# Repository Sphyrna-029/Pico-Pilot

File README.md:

# Pico-Pilot WIP
A auto pilot for land/air/sea based robots built on the RP2350B/RP2354B. Supports 2D waypoint missions, telemetry, and custom vehicle configuration. 
Requires simple_pid and warnings packages.

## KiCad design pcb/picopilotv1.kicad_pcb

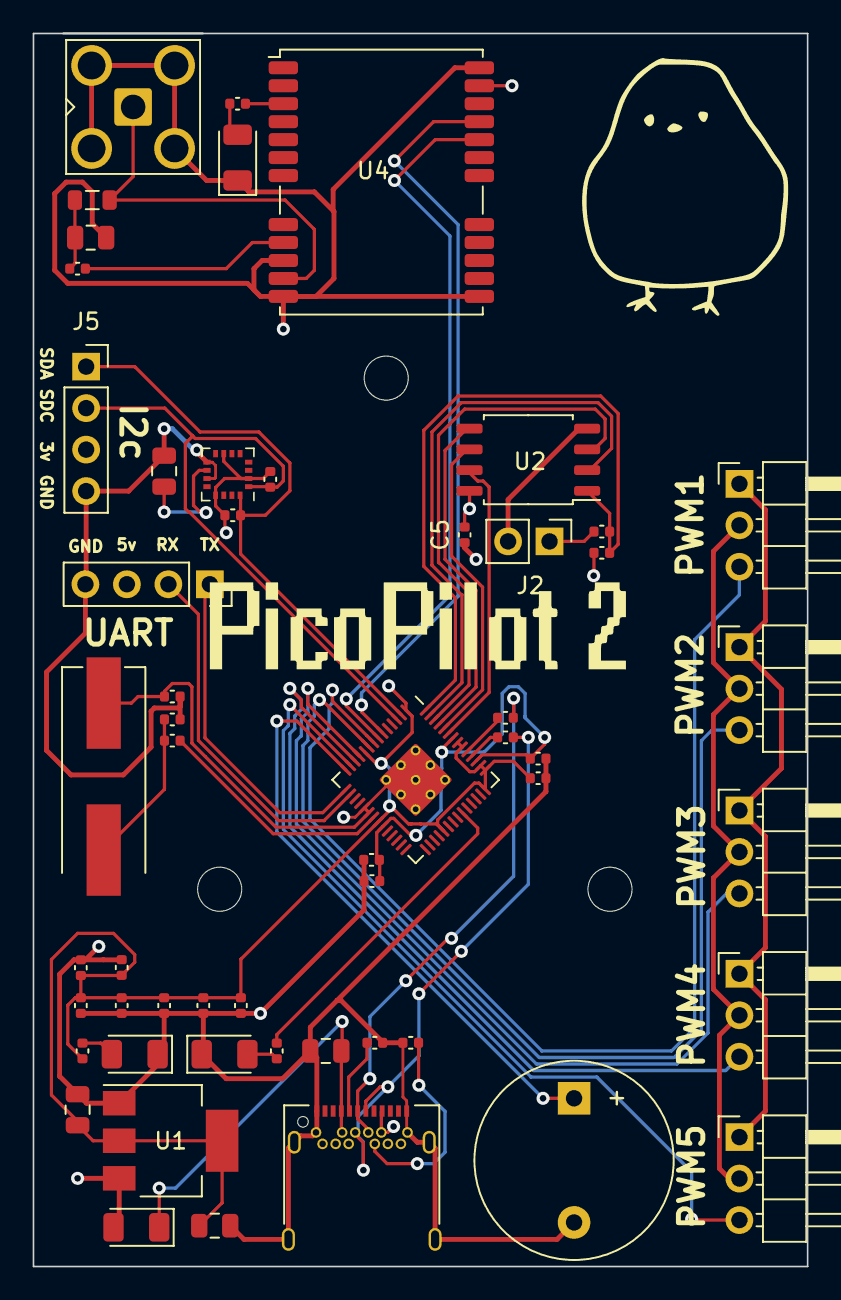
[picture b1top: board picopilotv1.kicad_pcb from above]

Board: 4 copper layers, 47.4 x 75.5 mm, 58 parts (0 on the bottom side), 41 nets.

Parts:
BZ1: Buzzer; Buzzer_12x9.5RM7.6
C1, C4, C17: 10u; C_0805_2012Metric
C2, C3: 27p; C_0402_1005Metric
C5, C6, C7, C9, C11, C12, C13, C14, C15, C16: 100n; C_0402_1005Metric
C8, C10: 1u; C_0402_1005Metric
C18: 10n; C_0805_2012Metric
C19: 4.7uf; C_0805_2012Metric
D1: DIODE; D_1206_3216Metric
D2, D3, D4: LED; LED_1206_3216Metric
H1, H2, H3, H4: MountingHole; MountingHole_2.7mm_M2.5
J1, J5: Telemetry; PinSocket_1x04_P2.54mm_Vertical
J2: Conn_01x02; PinHeader_1x02_P2.54mm_Vertical
J3: USB_C_Receptacle_USB2.0; USB_C_Receptacle_Amphenol_12401548E4-2A
J4: Conn_Coaxial; SMA_Amphenol_901-143_Horizontal
L1: 27nh; L_0805_2012Metric
P1: PWM1; PinHeader_1x03_P2.54mm_Horizontal
P2: PWM2; PinHeader_1x03_P2.54mm_Horizontal
P3: PWM3; PinHeader_1x03_P2.54mm_Horizontal
P4: PWM4; PinHeader_1x03_P2.54mm_Horizontal
P5: PWM5; PinHeader_1x03_P2.54mm_Horizontal
R1, R5, R6, R7, R9: 1k; C_0402_1005Metric
R2: DNF; C_0402_1005Metric
R3, R4: 27; C_0402_1005Metric
R8: 10; C_0402_1005Metric
R10, R11: 4.7k; C_0402_1005Metric
R13, R14: 5.11k; C_0402_1005Metric
U1: NCP1117-3.3_SOT223; SOT-223-3_TabPin2
U2: W25Q128JVS; SOIC-8_5.23x5.23mm_P1.27mm
U3: RP2040; RP2040-QFN-56
U4: NEO-M8M; ublox_NEO
U5: IST8308; LGA-16_3x3mm_P0.5mm
Y1: ABLS-12.000MHZ-B4-T; Crystal_SMD_HC49-US

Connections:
+1V1: C6.1, C7.1, C8.1, U3.23 (DVDD), U3.45 (VREG_VOUT), U3.50 (DVDD)
+3V3: C4.1, C5.1, C9.1, C10.1, C11.1, C12.1, C13.1, C14.1, C15.1, C16.1, C17.1, J5.3, R2.1, R6.1, R10.1, R11.1, U1.2 (VO), U2.8 (VCC), U3.1 (IOVDD), U3.10 (IOVDD), U3.22 (IOVDD), U3.33 (IOVDD), U3.42 (IOVDD), U3.43 (ADC_AVDD), U3.44 (VREG_IN), U3.48 (USB_VDD), U3.49 (IOVDD), U4.23 (VCC), U5.2 (AVDD), U5.7 (VPP), U5.13 (DVDD)
+5V: D1.2 (A), J1.3, P1.2, P2.2, P3.2, P4.2, P5.2, U1.3 (VI)
/GPIO0: J5.1, R11.2, U3.2 (GPIO0), U5.16 (SDA)
/GPIO1: J5.2, R10.2, U3.3 (GPIO1), U5.1 (SCL)
/GPIO4: U3.6 (GPIO4), U4.21 (RXD/SPI_MOSI)
/GPIO5: U3.7 (GPIO5), U4.20 (TXD/SPI_MISO)
/GPIO6: P1.3, U3.8 (GPIO6)
/GPIO7: P2.3, U3.9 (GPIO7)
/GPIO8: P3.3, U3.11 (GPIO8)
/GPIO9: P4.3, U3.12 (GPIO9)
/GPIO10: P5.3, U3.13 (GPIO10)
/GPIO11: BZ1.1 (-), U3.14 (GPIO11)
/GPIO12: J1.1, U3.15 (GPIO12)
/GPIO13: J1.2, U3.16 (GPIO13)
/GPIO25: R7.1, U3.37 (GPIO25)
/QSPI_SCLK: U2.6 (CLK), U3.52 (QSPI_SCLK)
/QSPI_SD0: U2.5 (DI(IO0)), U3.53 (QSPI_SD0)
/QSPI_SD1: U2.2 (DO(IO1)), U3.55 (QSPI_SD1)
/QSPI_SD2: U2.3 (IO2), U3.54 (QSPI_SD2)
/QSPI_SD3: U2.7 (IO3), U3.51 (QSPI_SD3)
/QSPI_SS: R1.1, R2.2, U2.1 (~CS), U3.56 (QSPI_SS)
/USB_D+: J3.A6 (D+), J3.B6 (D+), R3.1
/USB_D-: J3.A7 (D-), J3.B7 (D-), R4.1
/XOUT: R5.1, U3.21 (XOUT)
/~USB_BOOT: J2.1, R1.2
GND: BZ1.2 (+), C1.2, C2.1, C2.2, C3.2, C4.2, C5.2, C6.2, C7.2, C8.2, C9.2, C10.2, C11.2, C12.2, C13.2, C14.2, C15.2, C16.2, C17.2, C18.1, C19.2, D2.1 (K), D3.1 (K), D4.1 (K), J1.4, J2.2, J3.A1 (GND), J3.A12 (GND), J3.B1 (GND), J3.B12 (GND), J3.S1 (SHIELD), J4.2 (Ext), J5.4, P1.1, P2.1, P3.1, P4.1, P5.1, R13.2, R14.2, U1.1 (GND), U2.4 (GND), U3.19 (TESTEN), U3.20 (XIN), U3.57 (GND), U4.10 (GND), U4.12 (GND), U4.13 (GND), U4.24 (GND), U5.9 (VSS), U5.11 (VSS), Y1.1
unnamed: C3.1, R5.2, Y1.2
unnamed: C18.2, L1.1, R8.2
unnamed: C19.1, U5.10 (C1)
unnamed: D2.2 (A), R6.2
unnamed: D3.2 (A), R7.2
unnamed: D4.2 (A), R9.2
unnamed: J4.1 (In), L1.2, U4.11 (RF_IN)
unnamed: R3.2, U3.47 (USB_DP)
unnamed: R4.2, U3.46 (USB_DM)
unnamed: R8.1, U4.9 (VCC_RF)
unnamed: R9.1, U4.3 (TIMEPULSE)
unnamed: J3.A5 (CC1), R13.1
unnamed: J3.B5 (CC2), R14.1
VBUS: C1.1, D1.1 (K), J3.A4 (VBUS), J3.A9 (VBUS), J3.B4 (VBUS), J3.B9 (VBUS)

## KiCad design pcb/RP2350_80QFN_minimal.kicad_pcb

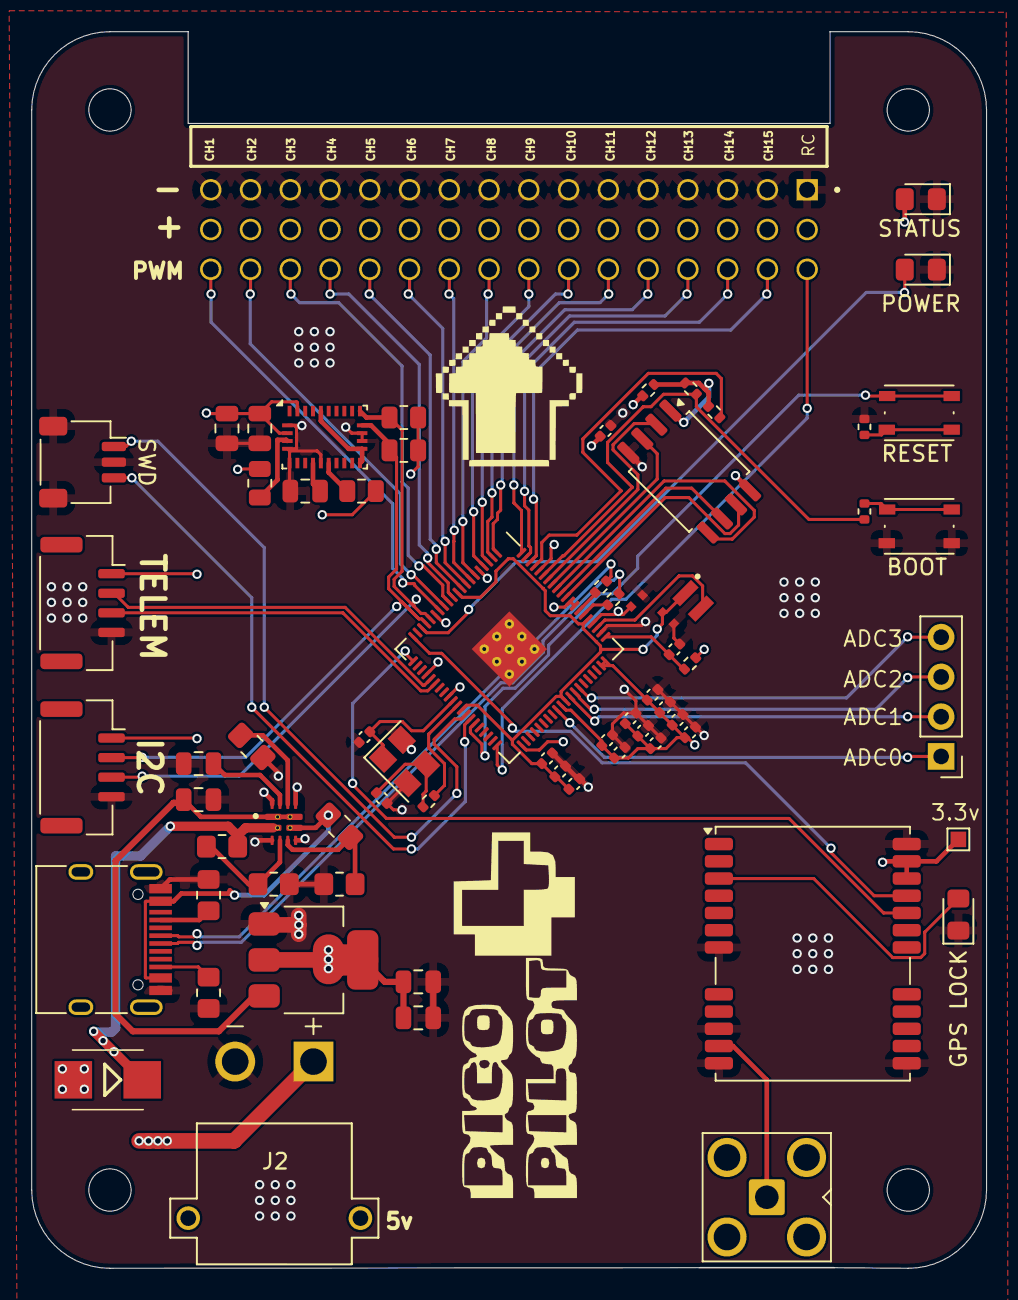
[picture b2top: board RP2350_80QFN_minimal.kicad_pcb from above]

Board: 4 copper layers, 61.0 x 79.0 mm, 72 parts (0 on the bottom side), 68 nets.

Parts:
BOOT: SW_Push; SW_Push_1P1T_NO_Vertical_Wuerth_434133025816
C1, C5, C19: 10u; C_0805_2012Metric
C2, C8, C11, C12, C13, C14, C15, C16, C17, C18, C20, C21: 100n; C_0402_1005Metric
C3, C4: 15p; C_0402_1005Metric
C6, C7: 4.7u; C_0402_1005Metric_small_pads
C9, C10: 4.7u; C_0402_1005Metric
C22: 100nF; C_0805_2012Metric
C23: 120nF; C_0805_2012Metric
C24: 6.8nF; C_0805_2012Metric
C25: 0.01u; C_0805_2012Metric
D1, D2, D3: LED; LED_0805_2012Metric_Pad1.15x1.40mm_HandSolder
D4: SS56; SMB
H1, H2, H3, H4: MountingHole; MountingHole_2.7mm_M2.5
J1: USB_C_Receptacle_USB2.0_14P; USB_C_Receptacle_HRO_TYPE-C-31-M-12
J2: XT30PW-M; AMASS_XT30PW-M
J3, J6: Conn_01x04_Pin; Molex_CLIK-Mate_502386-0470_1x04-1MP_P1.25mm_Horizontal
J4: SM03B-SRSS-TB; JST_SH_SM03B-SRSS-TB_1x03-1MP_P1.00mm_Horizontal
J5: TSW-116-08-G-T-RA; SAMTEC_TSW-116-08-G-T-RA
J7: Conn_01x04_Pin; PinHeader_1x04_P2.54mm_Vertical
J8: Conn_Coaxial_Small; SMA_Amphenol_901-143_Horizontal
L1: 3.3u; L_pol_2016
R1, R9: DNF; R_0402_1005Metric
R2, R4, R6: 1k; R_0402_1005Metric
R3: 33; R_0402_1005Metric
R5, R12: 5.1k; R_0805_2012Metric_Pad1.20x1.40mm_HandSolder
R7, R8: 27; R_0402_1005Metric
R10: 0; R_0402_1005Metric
R11, R15: 10k; R_0805_2012Metric
R13, R14: 4.7k; R_0805_2012Metric
R16: 51.1k; R_0805_2012Metric_Pad1.20x1.40mm_HandSolder
R17, R19: 23.7k; R_0805_2012Metric_Pad1.20x1.40mm_HandSolder
R18, R20: 5k; R_0805_2012Metric_Pad1.20x1.40mm_HandSolder
RESET: SW_Push; SW_Push_1P1T_NO_Vertical_Wuerth_434133025816
TP1: TestPoint; TestPoint_Pad_1.0x1.0mm
U1: RP2350_80QFN; RP2350-QFN-80-1EP_10x10_P0.4mm_EP3.4x3.4mm_ThermalVias
U2: NCP1117-3.3_SOT223; SOT-223-3_TabPin2
U3: W25Q128JVS; SOIC-8_5.23x5.23mm_P1.27mm
U4: NEO-M9N; ublox_NEO
U5: BNO055; LGA-28_5.2x3.8mm_P0.5mm
U6: TPS2121RUXR; IC_TPS2121RUXR
Y1: ABM8-272-T3; Crystal_SMD_3225-4Pin_3.2x2.5mm

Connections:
+1V1: C7.1, C8.1, C10.1, C11.1, L1.1, U1.10 (DVDD), U1.32 (DVDD), U1.51 (DVDD), U1.65 (VREG_FB)
+3V3: C2.1, C5.1, C6.1, C12.1, C13.1, C14.1, C15.1, C16.1, C17.1, C18.1, C19.1, C20.1, C21.1, C23.2, C24.2, D2.2 (A), J3.1, J6.1, R1.1, R3.1, R11.1, R13.2, R14.2, R15.1, TP1.1, U1.5 (IOVDD), U1.15 (IOVDD), U1.24 (IOVDD), U1.29 (IOVDD), U1.41 (IOVDD), U1.50 (IOVDD), U1.59 (ADC_AVDD), U1.60 (IOVDD), U1.64 (VREG_VIN), U1.68 (USB_OTP_VDD), U1.69 (QSPI_IOVDD), U1.76 (IOVDD), U2.2 (VO), U3.8 (VCC), U4.22 (V_BCKP), U4.23 (VCC), U5.3 (VDD), U5.28 (VDDIO)
/FLASH_SS: R1.2, R9.2, R10.2, U3.1 (~CS)
/GPIO0: R9.1, U1.77 (GPIO0)
/GPIO1: J5.06, U1.78 (GPIO1)
/GPIO2: J5.09, U1.79 (GPIO2)
/GPIO3: J5.12, U1.80 (GPIO3)
/GPIO4: J5.15, U1.1 (GPIO4)
/GPIO5: J5.18, U1.2 (GPIO5)
/GPIO6: J5.21, U1.3 (GPIO6)
/GPIO7: J5.24, U1.4 (GPIO7)
/GPIO8: J5.27, U1.6 (GPIO8)
/GPIO9: J5.30, U1.7 (GPIO9)
/GPIO10: J5.33, U1.8 (GPIO10)
/GPIO11: J5.36, U1.9 (GPIO11)
/GPIO12: J5.39, U1.11 (GPIO12)
/GPIO13: J5.42, U1.12 (GPIO13)
/GPIO14: J5.45, U1.13 (GPIO14)
/GPIO15: J5.48, U1.14 (GPIO15)
/GPIO18: D1.2 (A), U1.18 (GPIO18)
/GPIO20: U1.20 (GPIO20), U4.21 (RXD/SPI_MOSI)
/GPIO21: U1.21 (GPIO21), U4.20 (TXD/SPI_MISO)
/GPIO24: J3.2, U1.25 (GPIO24)
/GPIO25: J3.3, U1.26 (GPIO25)
/GPIO32: J5.03, U1.40 (GPIO32)
/GPIO40_ADC0: J7.1, U1.49 (GPIO40_ADC0)
/GPIO41_ADC1: J7.2, U1.52 (GPIO41_ADC1)
/GPIO42_ADC2: J7.3, U1.53 (GPIO42_ADC2)
/GPIO43_ADC3: J7.4, U1.54 (GPIO43_ADC3)
/QSPI_SCLK: U1.71 (QSPI_SCLK), U3.6 (CLK)
/QSPI_SD0: U1.72 (QSPI_SD0), U3.5 (DI(IO0))
/QSPI_SD1: U1.74 (QSPI_SD1), U3.2 (DO(IO1))
/QSPI_SD2: U1.73 (QSPI_SD2), U3.3 (IO2)
/QSPI_SD3: U1.70 (QSPI_SD3), U3.7 (IO3)
/QSPI_SS: R6.1, R10.1, U1.75 (QSPI_SS)
/RUN: RESET.2, U1.35 (RUN)
/SWCLK: J4.1, U1.33 (SWCLK)
/SWD: J4.3, U1.34 (SWD)
/USB_D+: J1.A6 (D+), R7.1
/USB_D-: J1.A7 (D-), R8.1
/VREG_AVDD: C9.1, R3.2, U1.61 (VREG_AVDD)
/VREG_LX: L1.2, U1.63 (VREG_LX)
/XIN: C3.1, U1.30 (XIN), Y1.1
/XOUT: R2.1, U1.31 (XOUT)
/~USB_BOOT: BOOT.2, R6.2
GND: BOOT.1, C1.2, C2.2, C3.2, C4.2, C5.2, C6.2, C7.2, C8.2, C9.2, C10.2, C11.2, C12.2, C13.2, C14.2, C15.2, C16.2, C17.2, C18.2, C19.2, C20.2, C21.2, C22.2, C23.1, C24.1, C25.2, D1.1 (K), D2.1 (K), D3.1 (K), J1.A1 (GND), J1.A12 (GND), J1.B1 (GND), J1.B12 (GND), J2.N, J3.4, J4.2, J4.MP (MountPin), J5.01, J5.04, J5.07, J5.10, J5.13, J5.16, J5.19, J5.22, J5.25, J5.28, J5.31, J5.34, J5.37, J5.40, J5.43, J5.46, J6.4, R4.2, R5.1, R12.1, R16.1, R18.1, R20.1, U1.62 (VREG_PGND), U1.81 (GND), U2.1 (GND), U3.4 (GND), U4.7 (VDD_USB), U4.10 (GND), U4.12 (GND), U4.13 (GND), U4.24 (GND), U5.2 (GND), U5.5 (PS1), U5.6 (PS0), U5.10 (BL_IND), U5.17 (COM3), U5.18 (COM2), U6.3 (CP2), U6.6 (PR1), U6.9 (ST), U6.12 (GND), Y1.2, Y1.4
unnamed: C4.1, R2.2, Y1.3
unnamed: D3.2 (A), U4.3 (TIMEPULSE)
unnamed: D4.C, R17.2, U6.2 (IN2), U6.2_1 (IN2)
unnamed: J1.A5 (CC1), R5.2
unnamed: J1.B5 (CC2), R12.2
unnamed: J8.1 (In), U4.11 (RF_IN)
unnamed: R4.1, RESET.1
unnamed: R8.2, U1.66 (USB_DM)
unnamed: R7.2, U1.67 (USB_DP)
unnamed: C22.1, U5.9 (CAP)
unnamed: U5.15 (GNDIO), U5.16 (GNDIO), U5.25 (GNDIO)
unnamed: R11.2, U5.4 (~BOOT_LOAD_PIN)
unnamed: R15.2, U5.11 (~RESET)
unnamed: R16.2, U6.10 (ILIM)
unnamed: R19.1, R20.2, U6.5 (OV1)
unnamed: R17.1, R18.2, U6.4 (OV2)
unnamed: C25.1, U6.11 (SS)
SDA: J6.3, R13.1, U1.16 (GPIO16), U5.20 (COM0)
SDL: J6.2, R14.1, U1.17 (GPIO17), U5.19 (COM1)
USBV: J1.A4 (VBUS), J1.A9 (VBUS), J1.B4 (VBUS), J1.B9 (VBUS), R19.2, U6.7 (IN1), U6.7_1 (IN1)
VBUS: D4.A, J2.P, J5.02, J5.05, J5.08, J5.11, J5.14, J5.17, J5.20, J5.23, J5.26, J5.29, J5.32, J5.35, J5.38, J5.41, J5.44, J5.47
VOUT: C1.1, U2.3 (VI), U6.1 (OUT), U6.1_1 (OUT), U6.8 (OUT), U6.8_1 (OUT)

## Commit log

2024-02-08 we're so back
2024-02-09 Functioning azimuth/heading
    Functioning azimuth and cardinal heading from mpu-9250. Maybe time for some real world trials?
2024-02-11 Circle Shortest Path
    Rudder control loop checks for shortest path on circle from current heading to target heading.
2024-08-15 Pico4!
2024-08-17 RP Diode
